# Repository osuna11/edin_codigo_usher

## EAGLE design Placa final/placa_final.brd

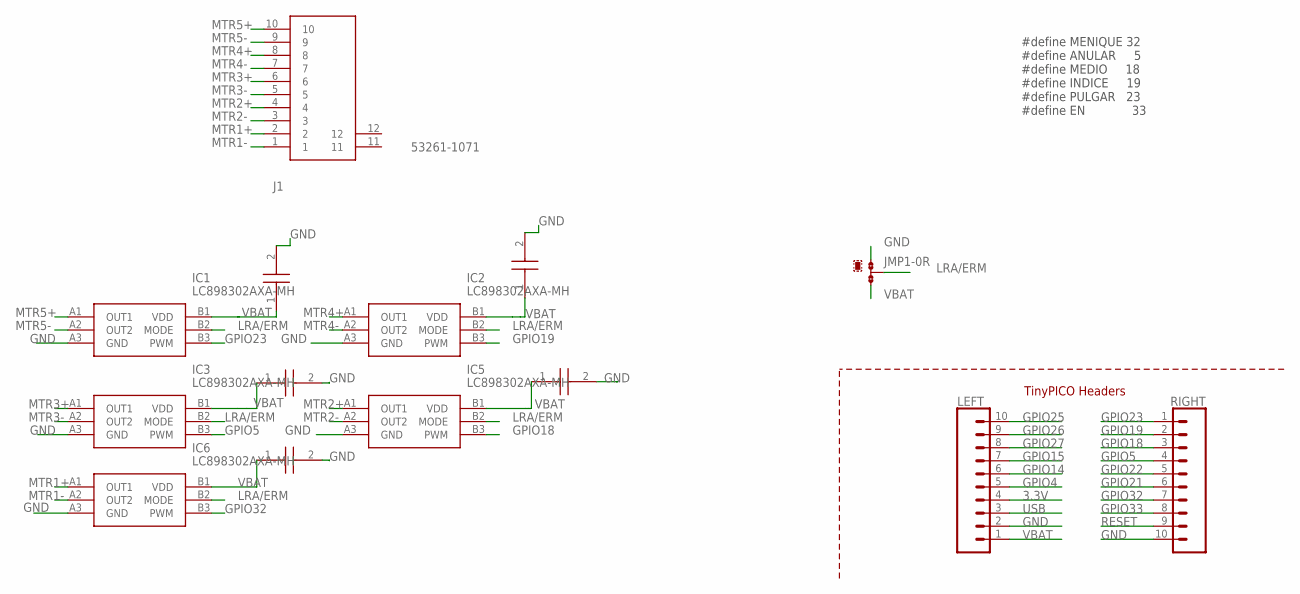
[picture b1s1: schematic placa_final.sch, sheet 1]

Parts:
C1, C2, C3, C4, C5: 0603B104K160CT; CAPC1608X87N
IC1, IC2, IC3, IC5, IC6: LC898302AXA-MH; BGA6C40P3X2_118X78X65
J1: 53261-1071; 532611071
JMP1: 0R-JUMPA; A0R-JMP
LEFT: TINYPICO_HEADER_10NO_SILK_PTH_FEMALE; 1X10_NO_SILK
RIGHT: TINYPICO_HEADER_10NO_SILK_PTH_FEMALE; 1X10_NO_SILK

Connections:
3.3V: LEFT.4; also elsewhere on the board
GND: C1.2, C2.2, C3.2, C4.2, C5.2, IC1.A3 (GND), IC2.A3 (GND), IC3.A3 (GND), IC5.A3 (GND), IC6.A3 (GND), JMP1.1, LEFT.2, RIGHT.10; also elsewhere on the board
GPIO4: LEFT.5; also elsewhere on the board
GPIO5: IC3.B3 (PWM), RIGHT.4
GPIO14: LEFT.6; also elsewhere on the board
GPIO15: LEFT.7; also elsewhere on the board
GPIO18: IC5.B3 (PWM), RIGHT.3
GPIO19: IC2.B3 (PWM), RIGHT.2
GPIO21: RIGHT.6
GPIO22: RIGHT.5
GPIO23: IC1.B3 (PWM), RIGHT.1
GPIO25: LEFT.10
GPIO26: LEFT.9
GPIO27: LEFT.8; also elsewhere on the board
GPIO32: IC6.B3 (PWM), RIGHT.7
GPIO33: RIGHT.8
LRA/ERM: IC1.B2 (MODE), IC2.B2 (MODE), IC3.B2 (MODE), IC5.B2 (MODE), IC6.B2 (MODE), JMP1.2
MTR1+: IC6.A1 (OUT1), J1.2
MTR1-: IC6.A2 (OUT2), J1.1
MTR2+: IC5.A1 (OUT1), J1.4
MTR2-: IC5.A2 (OUT2), J1.3
MTR3+: IC3.A1 (OUT1), J1.6
MTR3-: IC3.A2 (OUT2), J1.5
MTR4+: IC2.A1 (OUT1), J1.8
MTR4-: IC2.A2 (OUT2), J1.7
MTR5+: IC1.A1 (OUT1), J1.10
MTR5-: IC1.A2 (OUT2), J1.9
RESET: RIGHT.9; also elsewhere on the board
USB: LEFT.3
VBAT: C1.1, C2.1, C3.1, C4.1, C5.1, IC1.B1 (VDD), IC2.B1 (VDD), IC3.B1 (VDD), IC5.B1 (VDD), IC6.B1 (VDD), JMP1.3, LEFT.1

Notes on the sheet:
TinyPICO Headers
#define MENIQUE 32 #define ANULAR 5 #define MEDIO 18 #define INDICE 19 #define PULGAR 23 #define EN 33

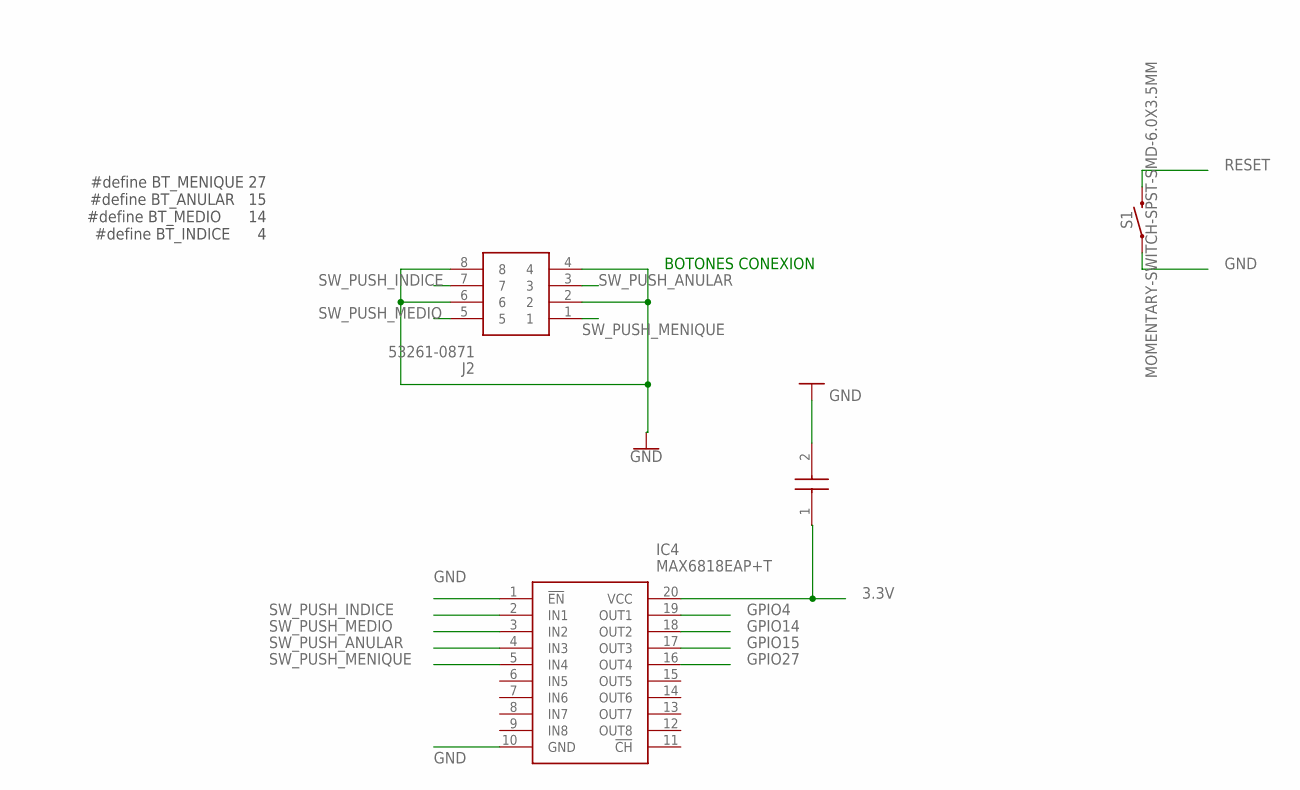
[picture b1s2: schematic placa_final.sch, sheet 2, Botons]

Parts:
C8: 0603B104K160CT; CAPC1608X87N
IC4: MAX6818EAP+T; SOP65P778X199-20N
J2: 53261-0871
S1: MOMENTARY-SWITCH-SPST-SMD-6.0X3.5MM; TACTILE_SWITCH_SMD_6.0X3.5MM

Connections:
3.3V: C8.1, IC4.20 (VCC); also elsewhere on the board
GND: C8.2, IC4.1 (!EN), IC4.10 (GND), J2.2, J2.4, J2.6, J2.8, S1.1; also elsewhere on the board
GPIO4: IC4.19 (OUT1); also elsewhere on the board
GPIO14: IC4.18 (OUT2); also elsewhere on the board
GPIO15: IC4.17 (OUT3); also elsewhere on the board
GPIO27: IC4.16 (OUT4); also elsewhere on the board
RESET: S1.2; also elsewhere on the board
SW_PUSH_ANULAR: IC4.4 (IN3), J2.3
SW_PUSH_INDICE: IC4.2 (IN1), J2.7
SW_PUSH_MEDIO: IC4.3 (IN2), J2.5
SW_PUSH_MENIQUE: IC4.5 (IN4), J2.1

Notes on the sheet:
#define BT_MENIQUE 27 #define BT_ANULAR 15 #define BT_MEDIO 14 #define BT_INDICE 4
BOTONES CONEXION

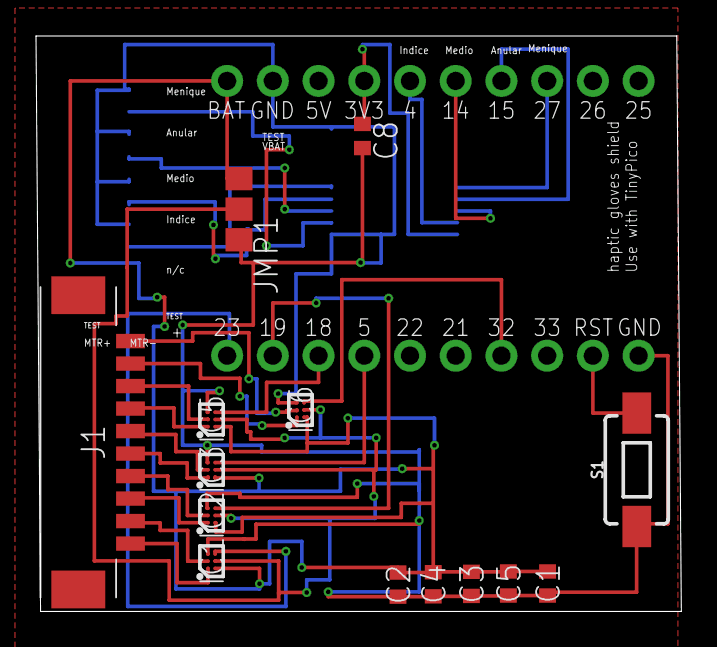
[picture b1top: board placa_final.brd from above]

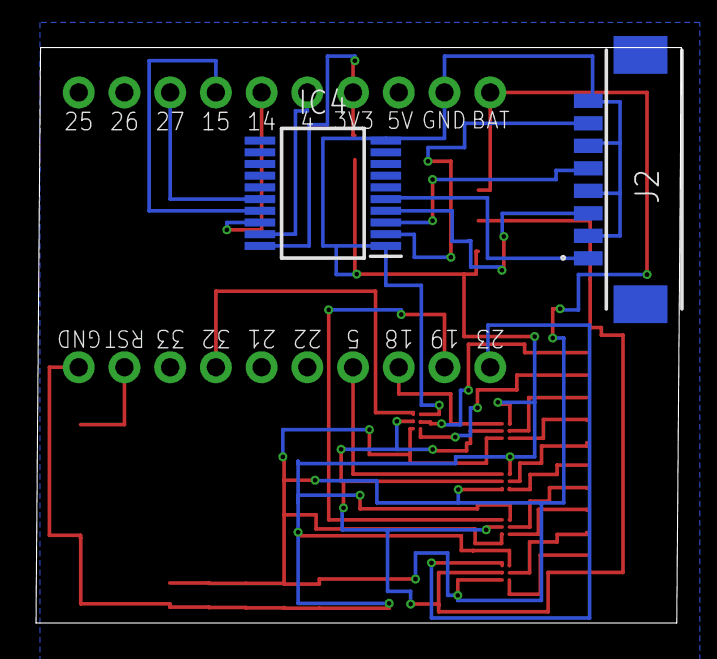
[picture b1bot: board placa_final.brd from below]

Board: 2 copper layers, 35.9 x 32.0 mm, 18 parts (2 on the bottom side), 28 nets.

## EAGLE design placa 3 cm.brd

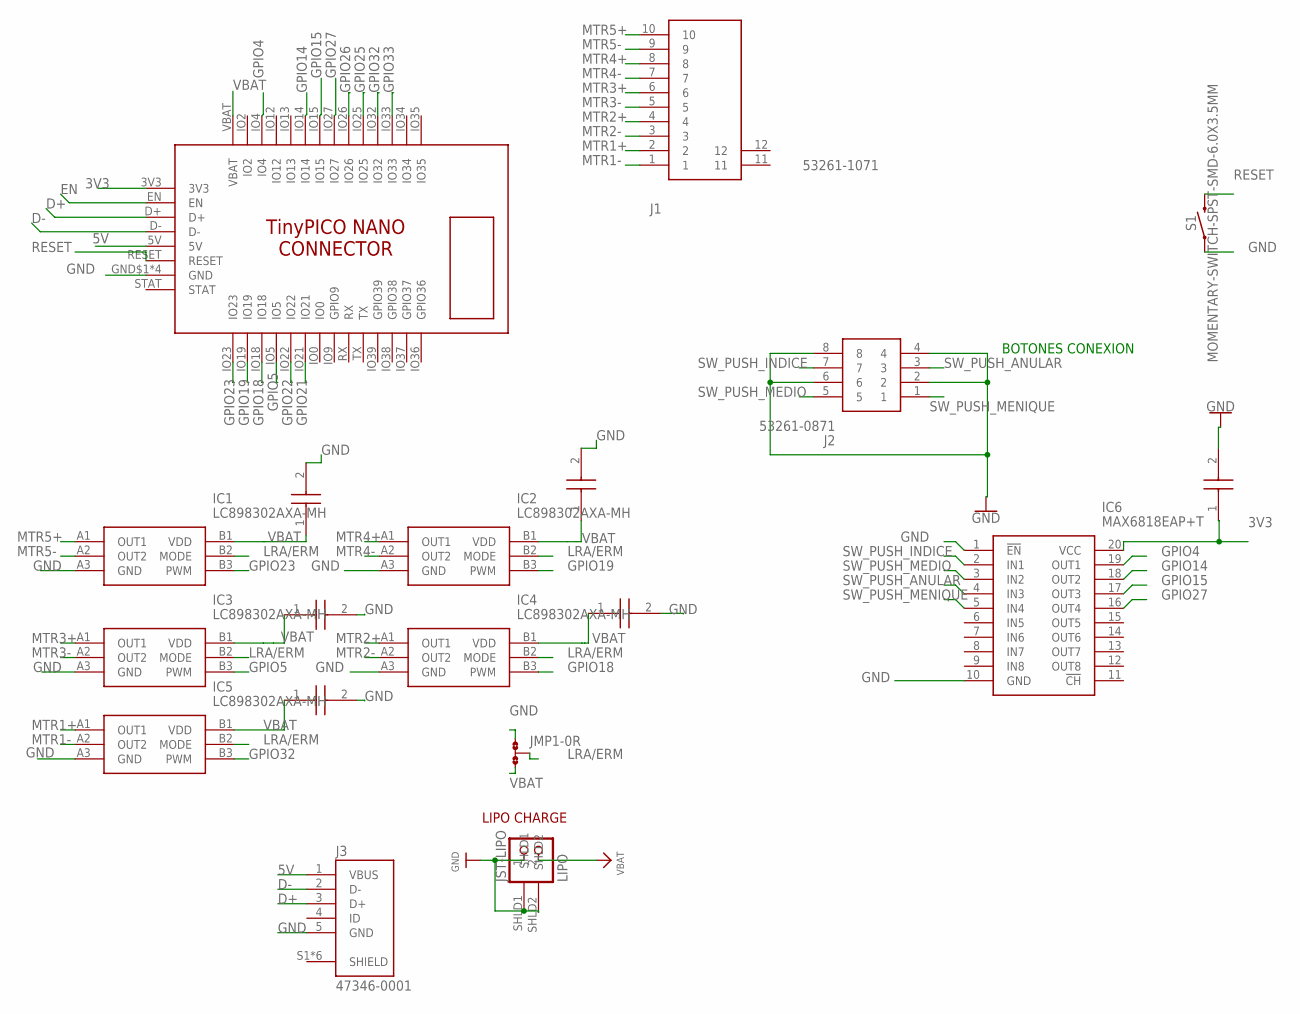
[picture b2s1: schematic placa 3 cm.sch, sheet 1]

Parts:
C1, C2, C3, C4, C5, C8: 0603B104K160CT; CAPC1608X87N
IC1, IC2, IC3, IC4, IC5: LC898302AXA-MH; BGA6C40P3X2_118X78X65
IC6: MAX6818EAP+T; SOP65P778X199-20N
J1: 53261-1071; 532611071
J2: 53261-0871
J3: 47346-0001; MOLEX_47346-0001
JMP1: 0R-JUMPA; A0R-JMP
JST-LIPO: LIPO; JSTPH2
S1: MOMENTARY-SWITCH-SPST-SMD-6.0X3.5MM; TACTILE_SWITCH_SMD_6.0X3.5MM
U$1: TINYPICO-NANO-CONNECTOR

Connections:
3V3: C8.1, IC6.20 (VCC), U$1.3V3
5V: J3.1 (VBUS), U$1.5V
D+: J3.3 (D+), U$1.D+
D-: J3.2 (D-), U$1.D-
EN: U$1.EN
GND: C1.2, C2.2, C3.2, C4.2, C5.2, C8.2, IC1.A3 (GND), IC2.A3 (GND), IC3.A3 (GND), IC4.A3 (GND), IC5.A3 (GND), IC6.1 (!EN), IC6.10 (GND), J2.2, J2.4, J2.6, J2.8, J3.5 (GND), JMP1.1, JST-LIPO.1, JST-LIPO.SHLD1, JST-LIPO.SHLD2, S1.1, U$1.GND$1 (GND), U$1.GND$2 (GND), U$1.GND$3 (GND), U$1.GND$4 (GND)
GPIO4: IC6.19 (OUT1), U$1.IO4
GPIO5: IC3.B3 (PWM), U$1.IO5
GPIO14: IC6.18 (OUT2), U$1.IO14
GPIO15: IC6.17 (OUT3), U$1.IO15
GPIO18: IC4.B3 (PWM), U$1.IO18
GPIO19: IC2.B3 (PWM), U$1.IO19
GPIO21: U$1.IO21
GPIO22: U$1.IO22
GPIO23: IC1.B3 (PWM), U$1.IO23
GPIO25: U$1.IO25
GPIO26: U$1.IO26
GPIO27: IC6.16 (OUT4), U$1.IO27
GPIO32: IC5.B3 (PWM), U$1.IO32
GPIO33: U$1.IO33
LRA/ERM: IC1.B2 (MODE), IC2.B2 (MODE), IC3.B2 (MODE), IC4.B2 (MODE), IC5.B2 (MODE), JMP1.2
MTR1+: IC5.A1 (OUT1), J1.2
MTR1-: IC5.A2 (OUT2), J1.1
MTR2+: IC4.A1 (OUT1), J1.4
MTR2-: IC4.A2 (OUT2), J1.3
MTR3+: IC3.A1 (OUT1), J1.6
MTR3-: IC3.A2 (OUT2), J1.5
MTR4+: IC2.A1 (OUT1), J1.8
MTR4-: IC2.A2 (OUT2), J1.7
MTR5+: IC1.A1 (OUT1), J1.10
MTR5-: IC1.A2 (OUT2), J1.9
RESET: S1.2, U$1.RESET
SW_PUSH_ANULAR: IC6.4 (IN3), J2.3
SW_PUSH_INDICE: IC6.2 (IN1), J2.7
SW_PUSH_MEDIO: IC6.3 (IN2), J2.5
SW_PUSH_MENIQUE: IC6.5 (IN4), J2.1
VBAT: C1.1, C2.1, C3.1, C4.1, C5.1, IC1.B1 (VDD), IC2.B1 (VDD), IC3.B1 (VDD), IC4.B1 (VDD), IC5.B1 (VDD), JMP1.3, JST-LIPO.2, U$1.VBAT

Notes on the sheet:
BOTONES CONEXION
LIPO CHARGE

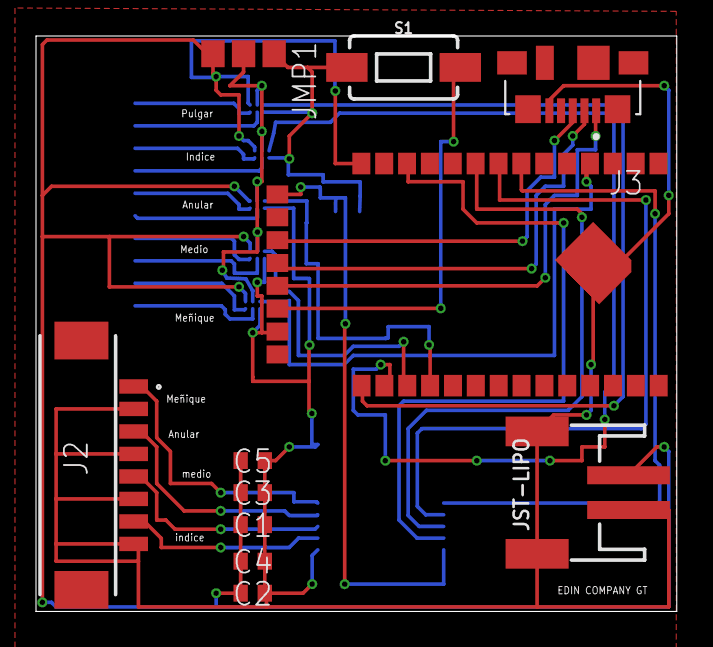
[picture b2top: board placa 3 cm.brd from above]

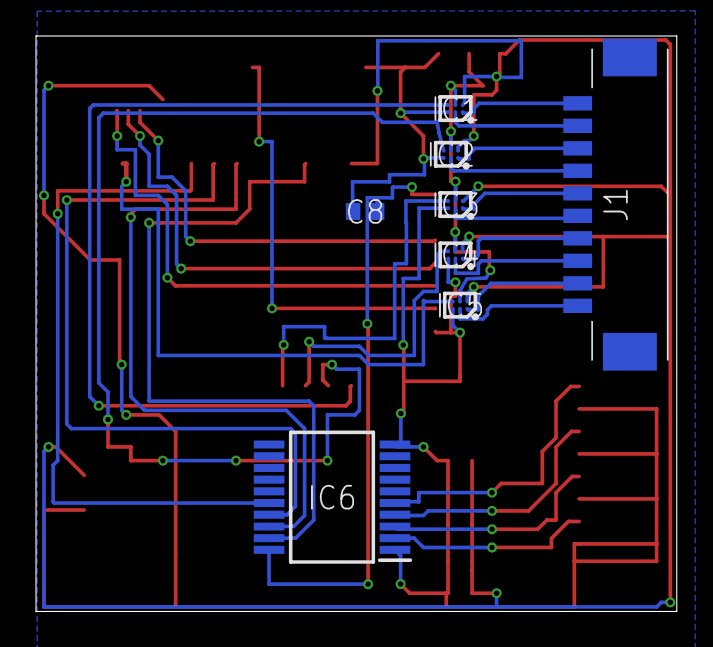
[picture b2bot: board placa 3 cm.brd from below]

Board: 2 copper layers, 35.6 x 32.0 mm, 19 parts (8 on the bottom side), 31 nets.

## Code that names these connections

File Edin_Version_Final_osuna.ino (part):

/**Attached interrupts
  *GPIO27   --->    SW_PUSH_MENIQUE
  *GPIO15   --->    SW_PUSH_ANULAR
  *GPIO14   --->    SW_PUSH_MEDIO
  *GPIO04   --->    SW_PUSH_INDICE
  ***********
  *PWM MOTORS 
  * GPIO23    --->    MTR_5
  * GPIO19    --->    MTR_4
  * GPIO18    --->    MTR_3
  * GPIO05    --->    MTR_2
  * GPIO32    --->    MTR_1
  * GPIO33    --->    ENABLE
  * 
   */
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
//Mapa de asignacion de puertos y canales para PWM ver esquematico para confirmar puertos.
#ifdef IZQUIERDA
vmotor pulgar = {23, 4}; //GPIO23 canal 4
vmotor indice = {19, 3}; //GPIO19 canal 3
vmotor medio = {18, 2}; //GPIO18 canal 2
vmotor anular = {5,  1}; //GPIO5 canal 1
vmotor menique = {32, 0}; //GPIO32 canal 0

#elif DERECHA

vmotor pulgar = {32, 0}; //GPIO23 canal 4
vmotor indice = {5,  1}; //GPIO19 canal 3
vmotor medio = {18, 2}; //GPIO18 canal 2
vmotor anular = {19, 3} //GPIO5 canal 1
vmotor menique = {23, 4};; //GPIO32 canal 0

#endif 
//*******************************************************************************Funcion de PWM para puerto 32 y 33 del ESP32
void aPinMode(int pinNum, int pinDir) {
  // Enable GPIO32 or 33 as output. 
  if (pinNum == 32 || pinNum == 33) {
    uint64_t gpioBitMask = (pinNum == 32) ? 1ULL<<GPIO_NUM_32 : 1ULL<<GPIO_NUM_33;
    gpio_mode_t gpioMode = (pinDir == OUTPUT) ? GPIO_MODE_OUTPUT : GPIO_MODE_INPUT;
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
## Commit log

2021-02-04 Add files via upload
    ya captura el tipo de movimiento y que dedos // falta hacerlo vibrar a traves de la funcion ledcwrite

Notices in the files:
parts and their libraries:
SparkFun-Switches: Licensing: Creative Commons ShareAlike 4.0 International - https://creativecommons.org/licenses/by-sa/4.0
microbuilder: This work is placed in the public domain, and may be freely used for commercial and non-commercial work with the following conditions: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
